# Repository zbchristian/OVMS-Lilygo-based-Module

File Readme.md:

Open-Vehicle-Monitoring-System: Module based on Lilygo T-Call A7670E V1.0/V1.1
==============================================================================
The Lilygo T-Call modules provide most of the hardware required for an OVMS module:
- ESP32-WROVER E with 4MB Flash and 8MB PSRAM
- Simcom A7670E 4G modem with GPS 
- Included antennas for 4G and GPS
- USB-C port for programming and powering during testing
- ext 5V powering possible via pin
- Price is around 35€ + tax

**This module supports only 2 CAN buses. This might limit the suitability for your car!**

OVMS Requirements
----------------- 
- Connection to OBD-II connector
- Powering via 12V of the OBD-II connector
- OBD-II to DSub-9 cable 

Communication with the car via CAN-bus requires
- Physical layer(s) and CAN controller
- 12V to 5V DC/DC converter and including filtering

Hardware
========
The Lilygo board is placed onto a motherboard, either into a socket, or the pins can be directly soldered to the board. The motherboard provides the voltage for the Lilygo board and the DSub-9 connector to connect to the OBD-II.
The board revision B is suitable for the T-Call version 1.0 and 1.1 (different GPIO mapping).

The image shows the module, the antennas and the 3D printed case (Freecad and Step files availybe in the `CAD` folder). The motherboard slides into slots and the lid will hold it in place.
The lid allows to store the GPS antenna, but allows to add SMA connectors for external antennas as well. The 4G antenna can be stored in a 1mm high compartment inside the case.

*The Lilygo based module and case. The GPS-antenna is placed into a corresponding slot in the lid of the case*

The chosen orientation (Simcom 7670 on the top) of the Lilygo board allows for easy access to the antenna connectors. The ESP32 WROVER E is in this case located on the bottom side.  

Features of the motherboard
---------------------------
The Lilygo T-Call is placed on a motherboard 
- size 49 x 98 mm²
- DSub-9 connector (pinout compatible standard OVMS module) to connect to the OBD-II
- 12V car battery input from the OBD-II, or a separate power souce 
- Fuse and filtering (common mode choke and capacitors) of the input voltage 
- DC/DC converter to provide the Lilygo board with 5V
    - Auto shutdown of the DC/DC converter at a voltage below 11.7V to prevent the drainage of the battery
    - A voltage of more than 11.9V is required to switch on again
- Two CAN busses are implemented
    - ESP32 internal requires only a physical layer
    - Second bus with an MCP2515 controller
    - Solder jumpers to enable 120 &Omega; bus termination resistors 
- Voltage divider to measure the battery voltage
- The schematic and board layout is provided for Autodesk Eagle
- The Gerber and bill of material is provided for the board production and assembly at JLCPCB 
- Nearly all components are placed on the bottom side of the PCB. This allows for an easy access, even when the Lilygo board is soldered to the motherboard
- 3D printable case to house the motherboard as well as the antennas
    - sufficient space in the lid to add SMA connectors for external antennas

*Top and bottom side of the module. Only a single CAN bus is assembled, because the module is used for a car with a single bus. Therefore the second physical layer and the MCP2515 is left empty*

Limitations
-----------
- The flash memory size of only 4MB Flash does no allow Over-the-Air updates of the firmware. So, each change requires access via the USB-C port 
- Only two CAN buses
- No GPIO extender
- No SD-Card support

Assembly related hints
----------------------
The Lilygo module can in principle be soldered directly to the board by using the provided pin headers. The board has to be mounted with the Simcom modem on the top side.
Using a precision socket and corresponding pin headers, the module can easliy be removed again, but should be secured by non conducting screws.
 
The DC-DC converter output voltage is defined by R8 and R9. The reference voltage is 0.8V, so with R8=100k and R9=18k, the output voltage is about 5.2V.
The Schottky diode reduces this by about 0.4V, hence the Lilygo module is powered by 4.8V. The diode is necessary to allow to provide power via the USB-C 
port at the same time, i.e. when flashing a new firmware. 

The DC-DC converter exhibits an enable input, which requires a minimum voltage to power on of 1.2V and to power off of 1.0V. The enable voltage is derived from the 
input voltage by means of the Zener diode Z1 and the voltage divider R3/R11. For a Zener voltage of 10V, the default values R3=100k and R11=220k lead to 
a minimal power on voltage of 11.8V and a maximal power off voltage of 11.5V. In case a different Zener voltage is used, the divider has to be adjusted accordingly. 

Firmware
--------
Except for the above mentioned limitation, the module is compatible with the standard OVMS firmware, BUT the pinout requires a remapping of the ESP32 pins.
This is implemented in the [OVMS repository](https://github.com/openvehicles/Open-Vehicle-Monitoring-System-3). 
- Follow the standard OVMS documentation to clone the above repository, install the required additional packages and install the required Espressif IDF
- In the folder `./vehicle/OVMS.V3` copy `support/sdkconfig.lilygo_tc` to `sdkconfig` and `support/partition4M.csv` to `partition4M.csv`
- Run `make menuconfig` and go to `Component config -> Opene Vehicle Monitoring System (OVMS) -> Hardware support`.
  - Hardware Version should be 3.1
  - Enable GPIO remapping under `Choose GPIO Mapping`
  - Now a new menu entry appears in `Hardware support` called `File with GPIO mapping`
	- For the above `sdkconfig`, the default file is `lilygo_tc_v11.h`. This is valid for the Rev B motherboard and a Lilygo A7670E T-Call V1.1
	- The GPIO mappings files are located in the folder `components/gpio_maps`
- Be sure, that the following OVMS components are disabled: MAX7317, external SWCAN, Over-The-Air update, SD card
- Disable the support for all cars (`vehicle support`) except for the one you are interested in. This is required to meet the limited space in the Flash memory for the firmware
  - For the default `partitions4M.csv`, the available space for the firmware is `0x2f0000 = 3080192B = 2.94MB`. The full firmware requires about 3.5MB.
  - **The support for the *Nissan Leaf* and *Renault Twizzy* should always be disabled, since these do not compile without the MAX7317 support.**  
- Follow the standard documentation to compile and flash the firmware via USB
  - Check the size of the firmware: `ls -la build/ovms3.bin`
- If the flash process is failing due to a too large firmware
  - disable some additional cars under `Vehicle support`
  - if no corresponding scripts are utilized, disable the Javascript support (under `OVMS3 library suppoprt`). This saves about 220kB
  - disable components which are not needed, like the *ZIP archive support* (`OVMS3 library support`) and the `OVMS3 component options` *Reverse Engineering tools*, *ECU scanning*, *File editor*, *Plugins*
- The above limitation for the firmware size can be reduced, by using a modified partition table ([`partitions4M_full.csv`](partitions4M_full.csv)) from this repository
  - This reduces the `FAT` partition, the storage for the OVMS configuration, from `1MB` to `512kB`, which might cause problems in your setup!
  - In this case the available space for the firmware is `0x370000 = 3604480B = 3.44MB`

Alternative GPIO mapping
-------
Alternative GPIO mapping files are available and can be placed in the folder [`components/gpio_maps`](https://github.com/openvehicles/Open-Vehicle-Monitoring-System-3/tree/master/vehicle/OVMS.V3/components/gpio_maps). 

Check the [Readme](https://github.com/openvehicles/Open-Vehicle-Monitoring-System-3/tree/master/vehicle/OVMS.V3/components/gpio_maps) for details about the naming of the GPIO pins and the format of the mapping files.

Known Issues
------------
- An outdated firmware version of the Simcom A7670E can cause connection problems. The firmware can be updated according to the
[Modem Firmware Update Guide](https://github.com/Xinyuan-LilyGO/LilyGO-T-A76XX/blob/main/docs/update_fw.md). 
This requires to solder an USB cable to the corresponding pins on the Lilygo board (see [here](https://github.com/Xinyuan-LilyGO/LilyGO-T-A76XX/issues/180)).

Disclaimer
==========
This design is provided as is. Use at your own risk.

Enjoy!

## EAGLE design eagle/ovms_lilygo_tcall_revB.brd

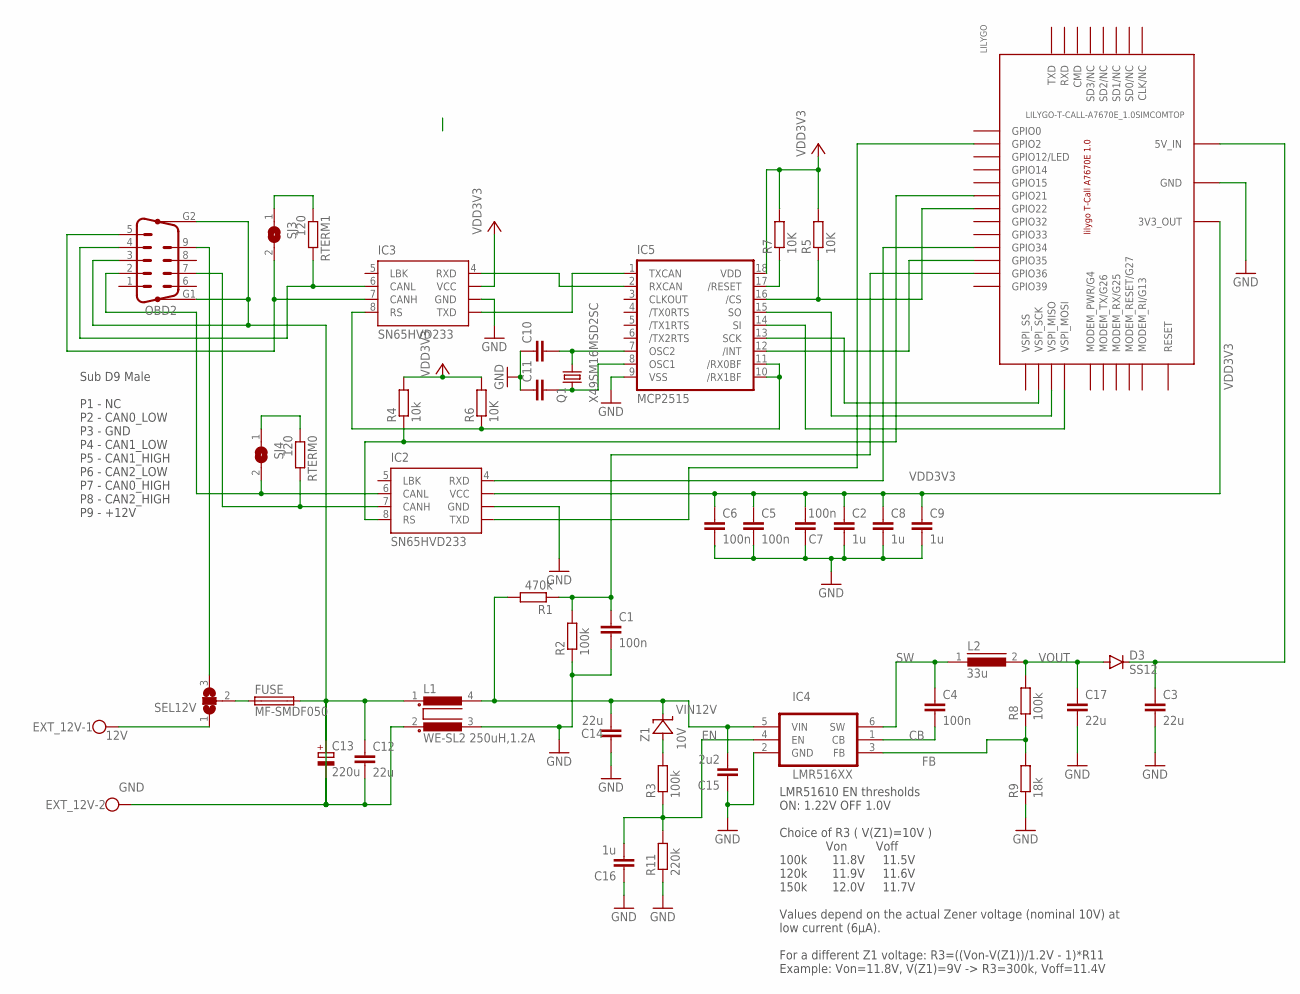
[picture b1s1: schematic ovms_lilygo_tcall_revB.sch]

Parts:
C1, C4, C5, C6, C7: 100n; C0805K
C2, C8, C9, C16: 1u; C0805K
C3, C17: 22u; C0805K
C10, C11: 22pF; C0805K
C12, C14: 22u; C1206K
C13: 220u; UD-8X10_NICHICON
C15: 2u2; C0805K
D3: SS12; SOD123
EXT_12V: GND; W237-102
FUSE: MF-SMDF050
IC2, IC3: SN65HVD233; SO-08
IC4: LMR516XX; SOT23-6
IC5: MCP2515; SO-18W
L1: WE-SL2 250uH,1.2A; CHOKE_SMD
L2: 33u; DR74
LILYGO: LILYGO-T-CALL-A7670E_1.0SIMCOMTOP; LILYGO-TCALL-A7670E_1.0
OBD2: M09HP
Q1: X49SM16MSD2SC; 11.4X4.5
R1: 470k; M0805
R2, R3, R8: 100k; M0805
R4: 10k; M0805
R5, R6, R7: 10K; M0805
R9: 18k; M0805
R11: 220k; M0805
RTERM0, RTERM1: 120; M0805
SEL12V: SJ2W; SJ_2
SJ3, SJ4: SJ
Z1: 10V; SOT23

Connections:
12V: C12.1, C13.+, FUSE.2, L1.1
CB: C4.2, IC4.1 (CB)
EN: C16.2, IC4.4 (EN), R3.1, R11.2
EXT12V: EXT_12V.1, SEL12V.1
FB: IC4.3 (FB), R8.1, R9.2
GND: C1.2, C2.2, C3.2, C5.2, C6.2, C7.1, C8.2, C9.2, C10.1, C11.1, C14.1, C15.1, C16.1, C17.2, IC2.2 (GND), IC3.2 (GND), IC4.2 (GND), IC5.9 (VSS), L1.3, LILYGO.1 (GND), LILYGO.7 (GND), LILYGO.25 (GND), R2.1, R9.1, R11.1
GND1: C12.2, C13.-, EXT_12V.2, L1.2, OBD2.3, OBD2.G1, OBD2.G2
unnamed: IC3.1 (TXD), IC5.1 (TXCAN)
unnamed: FUSE.1, SEL12V.2
unnamed: IC3.4 (RXD), IC5.2 (RXCAN)
unnamed: IC5.17 (/RESET), R7.1
unnamed: IC5.16 (/CS), LILYGO.3 (GPIO22), R5.1
unnamed: IC3.8 (RS), IC5.10 (/RX1BF), IC5.11 (/RX0BF), R6.1
unnamed: C10.2, IC5.7 (OSC2), Q1.2
unnamed: R3.2, Z1.1 (A)
unnamed: IC2.4 (RXD), LILYGO.34 (GPIO34)
unnamed: IC2.1 (TXD), LILYGO.15 (GPIO2)
unnamed: IC2.6 (CANL), OBD2.2, SJ4.2
unnamed: IC2.8 (RS), LILYGO.6 (GPIO21), R4.1
unnamed: IC2.7 (CANH), OBD2.7, RTERM0.2
unnamed: IC3.6 (CANL), OBD2.4, RTERM1.2
unnamed: IC3.7 (CANH), OBD2.5, SJ3.2
unnamed: C1.1, LILYGO.36 (GPIO36), R1.1, R2.2
unnamed: IC5.12 (/INT), LILYGO.33 (GPIO35)
unnamed: C11.2, IC5.8 (OSC1), Q1.1
unnamed: IC5.13 (SCK), LILYGO.9 (VSPI_SCK)
unnamed: IC5.15 (SO), LILYGO.8 (VSPI_MISO)
unnamed: IC5.14 (SI), LILYGO.2 (VSPI_MOSI)
unnamed: RTERM1.1, SJ3.1
unnamed: RTERM0.1, SJ4.1
OBD12V: OBD2.9, SEL12V.3
SW: C4.1, IC4.6 (SW), L2.1
VCC5V: C3.1, D3.C, LILYGO.20 (5V_IN)
VDD3V3: C2.1, C5.1, C6.1, C7.2, C8.1, C9.1, IC2.3 (VCC), IC3.3 (VCC), IC5.18 (VDD), LILYGO.38 (3V3_OUT), R4.2, R5.2, R6.2, R7.2
VIN12V: C14.2, C15.2, IC4.5 (VIN), L1.4, R1.2, Z1.3 (C)
VOUT: C17.1, D3.A, L2.2, R8.2

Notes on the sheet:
Sub D9 Male P1 - NC P2 - CAN0_LOW P3 - GND P4 - CAN1_LOW P5 - CAN1_HIGH P6 - CAN2_LOW P7 - CAN0_HIGH P8 - CAN2_HIGH P9 - +12V
LMR51610 EN thresholds ON: 1.22V OFF 1.0V Choice of R3 ( V(Z1)=10V ) Von Voff 100k 11.8V 11.5V 120k 11.9V 11.6V 150k 12.0V 11.7V Values depend on the actual Zener voltage (nominal 10V) at low current (6µA). For a different Z1 voltage: R3=((Von-V(Z1))/1.2V - 1)*R11 Example: Von=11.8V, V(Z1)=9V -> R3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

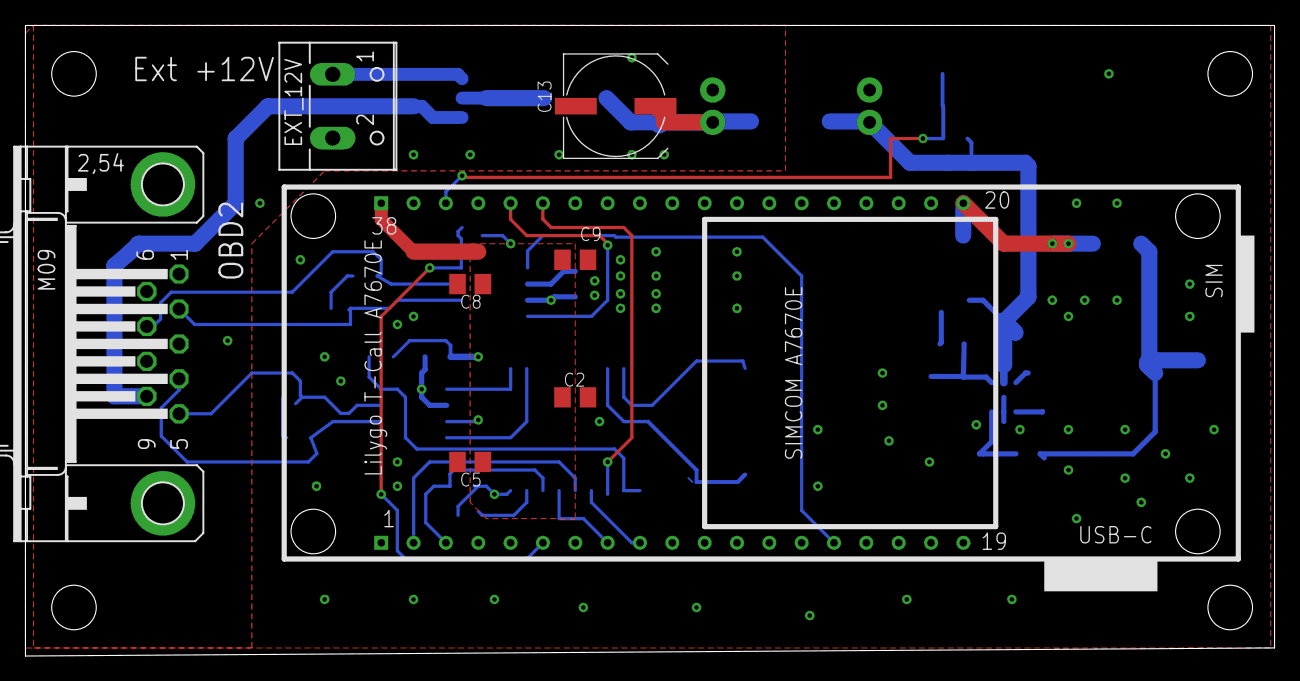
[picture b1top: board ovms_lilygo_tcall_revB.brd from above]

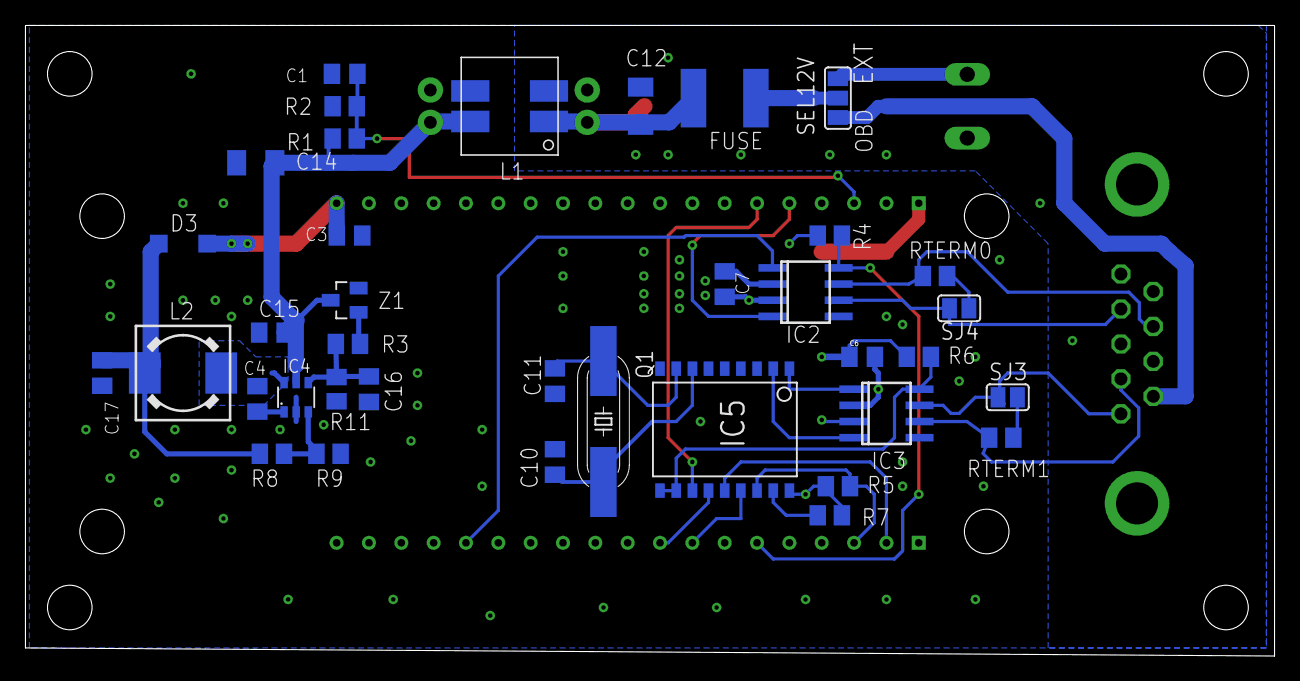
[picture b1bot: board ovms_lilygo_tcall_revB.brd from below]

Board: 2 copper layers, 98.1 x 49.5 mm, 45 parts (37 on the bottom side), 36 nets.

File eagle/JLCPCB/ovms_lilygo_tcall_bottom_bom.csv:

Comment,Designator,Footprint,LCSC Part #
1u,C16,C0805K,
2u2,C15,C0805K,
10K,R5 R6 R7,M0805,
10V,Z1,SOT23,
10k,R2 R4,M0805,
20k,R9,M0805,
22k,R3,M0805,
22pF,C10 C11,C0805K,
22u,C3,C0805K,
22u,C12,C3216,
22u,C14,C1206K,
22u,C17,C0805K,
33u,L2,DR74,
47k,R1 R11,M0805,
100k,R8,M0805,
100n,C1 C4 C6 C7,C0805K,
120,RTERM0 RTERM1,M0805,
LMR516XX,IC4,SOT23-6,
MCP2515,IC5,SO-18W,
MF-SMDF050,FUSE,MF-SMDF050,
SN65HVD233,IC2 IC3,SO-08,
SS12,D3,SOD123,
WE-SL2 250uH 1.2A,L1,CHOKE_SMD,
X49SM16MSD2SC,Q1,11.4X4.5,

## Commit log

2025-02-21 Motherboard and case for Lilygo-T-Call A7670E as OMS
2025-03-09 Correct width an hole position of case
2025-04-24 Add images of module
2025-04-24 Readme.md hinzugefügt
2025-04-24 Smaller images (500px wide)
2025-04-24 Readme.md aktualisiert
2025-04-26 Clean up Eagle
2025-04-26 Remove old case files
2025-04-26 Cleanup folders
2025-04-29 Adjust resistors for low current (DCDC off)
2025-05-16 Rename first version files to RevA and add RevB eagle files
2025-05-20 Add Readme
2025-05-20 eagle/RevA-obsolete/Readme.md aktualisiert
2025-05-23 Undelete Rev B eagle files
2025-05-23 Change schematic to increase default DCDC output voltage
2025-06-11 Replace CAN transceiver (TCAN330)
2025-09-22 Update documentation wrt modified OVMS repository

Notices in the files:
parts and their libraries:
crystal-geyer_V1_0: Copyright: Geyer-Electronic
